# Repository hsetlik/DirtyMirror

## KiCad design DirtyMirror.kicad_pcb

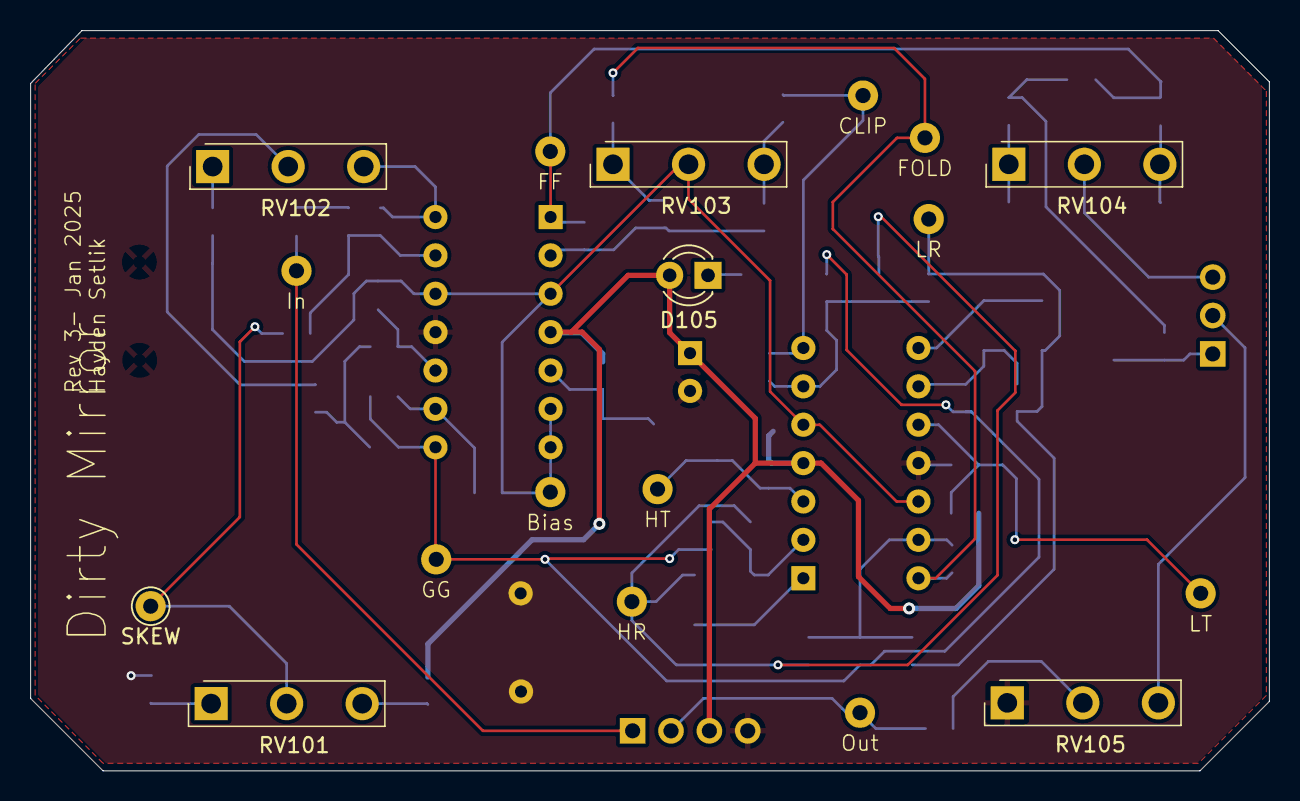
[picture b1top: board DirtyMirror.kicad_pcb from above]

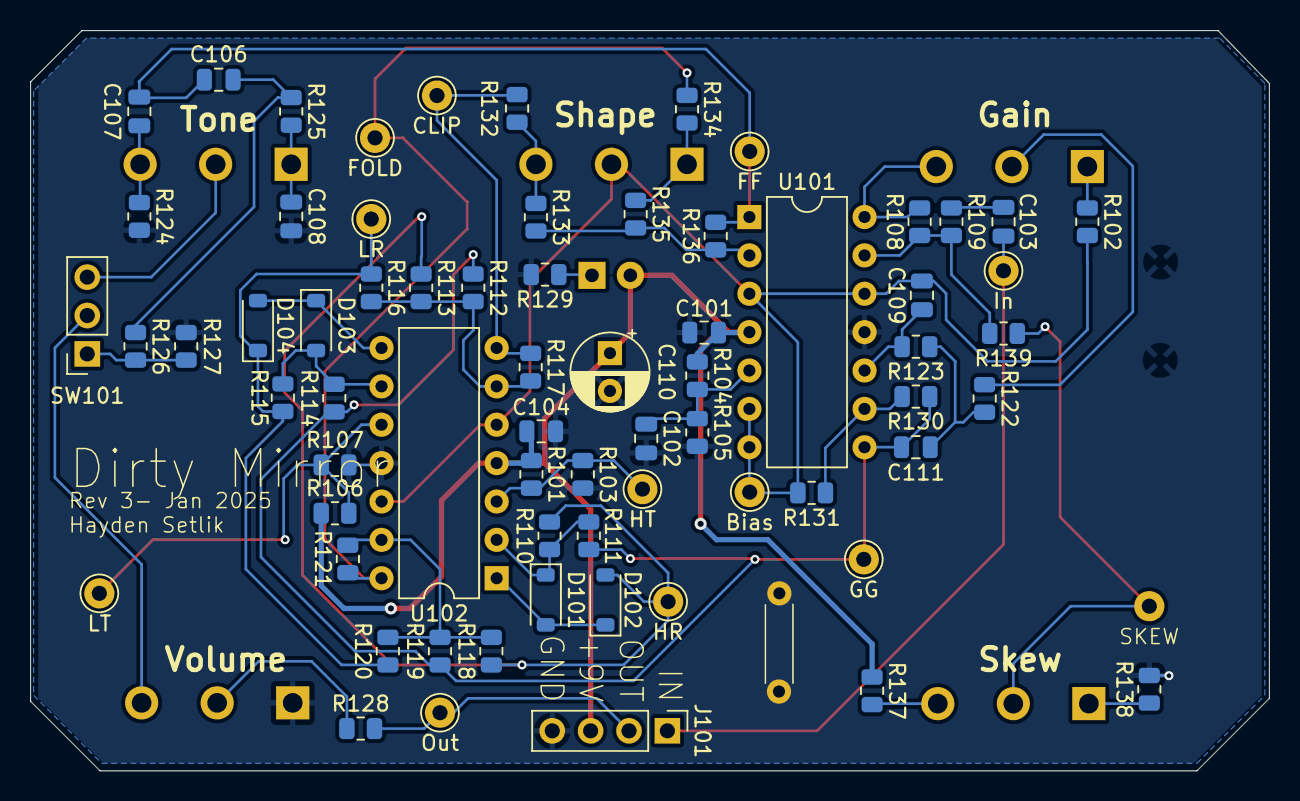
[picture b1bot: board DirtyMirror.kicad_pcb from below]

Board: 2 copper layers, 82.0 x 49.0 mm, 76 parts (69 on the bottom side), 42 nets.

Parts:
C101, C102, C104, C108: 100n; C_0805_2012Metric
C103, C106: 2u2; C_0805_2012Metric
C107, C109: 10n; C_0805_2012Metric
C110: 100u; CP_Radial_D5.0mm_P2.50mm
C111: 2n7; C_0805_2012Metric
D101, D102, D103, D104: 1N4148W; D_SOD-123
D105: LED; LED_D3.0mm
J101: PWR; PinHeader_1x04_P2.54mm_Vertical
J102: ScopeGroundLoop; THT_GND_WIRE
R101, R107, R118, R120, R132, R133, R134, R135, R138: 47k; R_0805_2012Metric
R102, R131: 10k; R_0805_2012Metric
R103, R106, R112, R117: 51k; R_0805_2012Metric
R104, R105, R109, R110, R111, R114, R115, R126, R127, R137, R139: 100k; R_0805_2012Metric
R108: 560k; R_0805_2012Metric
R113, R116, R119, R121: 56k; R_0805_2012Metric
R122, R123: 33k; R_0805_2012Metric
R124: 12k; R_0805_2012Metric
R125: 5k6; R_0805_2012Metric
R128: 220R; R_0805_2012Metric
R129: 4k7; R_0805_2012Metric
R130: 39k; R_0805_2012Metric
R136: 180k; R_0805_2012Metric
RV101, RV102, RV103, RV104: 100kB; Potentiometer_Alpha_RV16AF_42_Single_Long
RV105: 100kA; Potentiometer_Alpha_RV16AF_42_Single_Long
SW101: SW_SPDT; PinSocket_1x03_P2.54mm_Vertical
TP101: In; TestPoint_THTPad_D2.0mm_Drill1.0mm_VAL
TP102: Out; TestPoint_THTPad_D2.0mm_Drill1.0mm_VAL
TP103: LT; TestPoint_THTPad_D2.0mm_Drill1.0mm_VAL
TP104: HT; TestPoint_THTPad_D2.0mm_Drill1.0mm_VAL
TP105: Bias; TestPoint_THTPad_D2.0mm_Drill1.0mm_VAL
TP106: LR; TestPoint_THTPad_D2.0mm_Drill1.0mm_VAL
TP107: HR; TestPoint_THTPad_D2.0mm_Drill1.0mm_VAL
TP108: FF; TestPoint_THTPad_D2.0mm_Drill1.0mm_VAL
TP109: GG; TestPoint_THTPad_D2.0mm_Drill1.0mm_VAL
TP110: CLIP; TestPoint_THTPad_D2.0mm_Drill1.0mm_VAL
TP111: FOLD; TestPoint_THTPad_D2.0mm_Drill1.0mm_VAL
TP112: SKEW; TestPoint_THTPad_D2.0mm_Drill1.0mm_VAL
U101, U102: TL074; DIP-14_W7.62mm

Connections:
+9V: C101.1, C104.1, C110.1, D105.2 (A), J101.3, R101.1, R104.1, R106.1, R137.1, U101.4 (V+), U102.4 (V+)
/BYP: R126.2, R127.1, SW101.1 (A)
/Bias: C109.2, R102.2, R131.2, RV103.2, TP105.1, U101.3 (+), U101.6 (-), U101.7, U101.12 (+), U102.5 (+), U102.12 (+)
/Clip: R117.2, R132.1, TP110.1, U102.7
/Fold: R121.2, R134.1, TP111.1, U102.14
/FxFull: C106.1, C107.1, R136.2, TP108.1, U101.1
/Gtr_gain: C111.2, R111.1, R112.1, R114.1, R119.1, R130.2, TP109.1, U101.8
/HiRect: D102.2 (A), R110.2, R113.1, R118.1, TP107.1
/HiThresh: R101.2, R103.1, TP104.1, U102.3 (+)
/LoRect: D104.1 (K), R115.2, R116.1, R120.1, TP106.1
/LoThresh: R106.2, R107.1, TP103.1, U102.10 (+)
/TONE: RV104.2, SW101.3 (C)
/vSkew: R139.1, RV101.2, TP112.1
FX_IN: C103.1, J101.1, TP101.1
FX_OUT: J101.2, R128.2, TP102.1
GND: C101.2, C102.2, C104.2, C108.2, C110.2, J101.4, J102.1, R103.2, R105.2, R107.2, R124.2, R127.2, R129.2, R138.2, RV105.1, U101.11 (V-), U102.11 (V-)
unnamed: C103.2, R109.1
unnamed: C106.2, R125.1, R126.1
unnamed: C107.2, R124.1, RV104.3
unnamed: C108.1, R125.2, RV104.1
unnamed: C111.1, R122.2, R123.1
unnamed: D101.2 (A), D102.1 (K), U102.1
unnamed: D101.1 (K), R110.1, R111.2, U102.2 (-)
unnamed: D103.2 (A), R114.2, R115.1, U102.9 (-)
unnamed: D103.1 (K), D104.2 (A), U102.8
unnamed: D105.1 (K), R129.1
unnamed: R102.1, RV102.1
unnamed: R108.2, RV102.3, U101.14
unnamed: R122.1, RV102.2
unnamed: R128.1, RV105.2
unnamed: R132.2, R133.1, RV103.3
unnamed: R134.2, R135.1, RV103.1
unnamed: R137.2, RV101.3
unnamed: R138.1, RV101.1
unnamed: RV105.3, SW101.2 (B)
unnamed: R133.2, R135.2, R136.1, U101.2 (-)
unnamed: C102.1, R104.2, R105.1, U101.5 (+)
unnamed: C109.1, R123.2, U101.10 (+)
unnamed: R130.1, R131.1, U101.9 (-)
unnamed: R108.1, R109.2, R139.2, U101.13 (-)
unnamed: R112.2, R113.2, R116.2, R117.1, U102.6 (-)
unnamed: R118.2, R119.2, R120.2, R121.1, U102.13 (-)

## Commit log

2024-12-28 nicely labeled simulation
2024-12-28 schematic 1st pass
2024-12-28 footprints & layout
2024-12-28 sallen-key input stage
2024-12-28 prettified schematic
2024-12-29 routed & DRC passing
2025-01-10 rev2 simulation
2025-01-10 rev2 passive vals dialed in
2025-01-10 rev2 rough routing
2025-01-10 silkscreen, DRC passing
2025-01-16 pedal working, tweaked a few component values
2025-01-26 summing amp tweaks
2025-01-27 threshold/summing amp value tweaks
2025-01-27 optimized rev2 component values :)
2025-01-27 moved skew control to input amp
2025-01-27 rev3 minor tweaks
2025-01-27 silkscreen and spacing niceities
2025-02-02 component values
2025-08-25 changed schematic to reflect bodging
